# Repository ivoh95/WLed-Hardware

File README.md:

# WLed-Hardware
Collection of PCB designs and other hardware for the WLED project by Aircoookie

WLED Mini is a board intended for use with the wemos D1

WLED 01 is a board intended for use with the esp01

Currently WIP

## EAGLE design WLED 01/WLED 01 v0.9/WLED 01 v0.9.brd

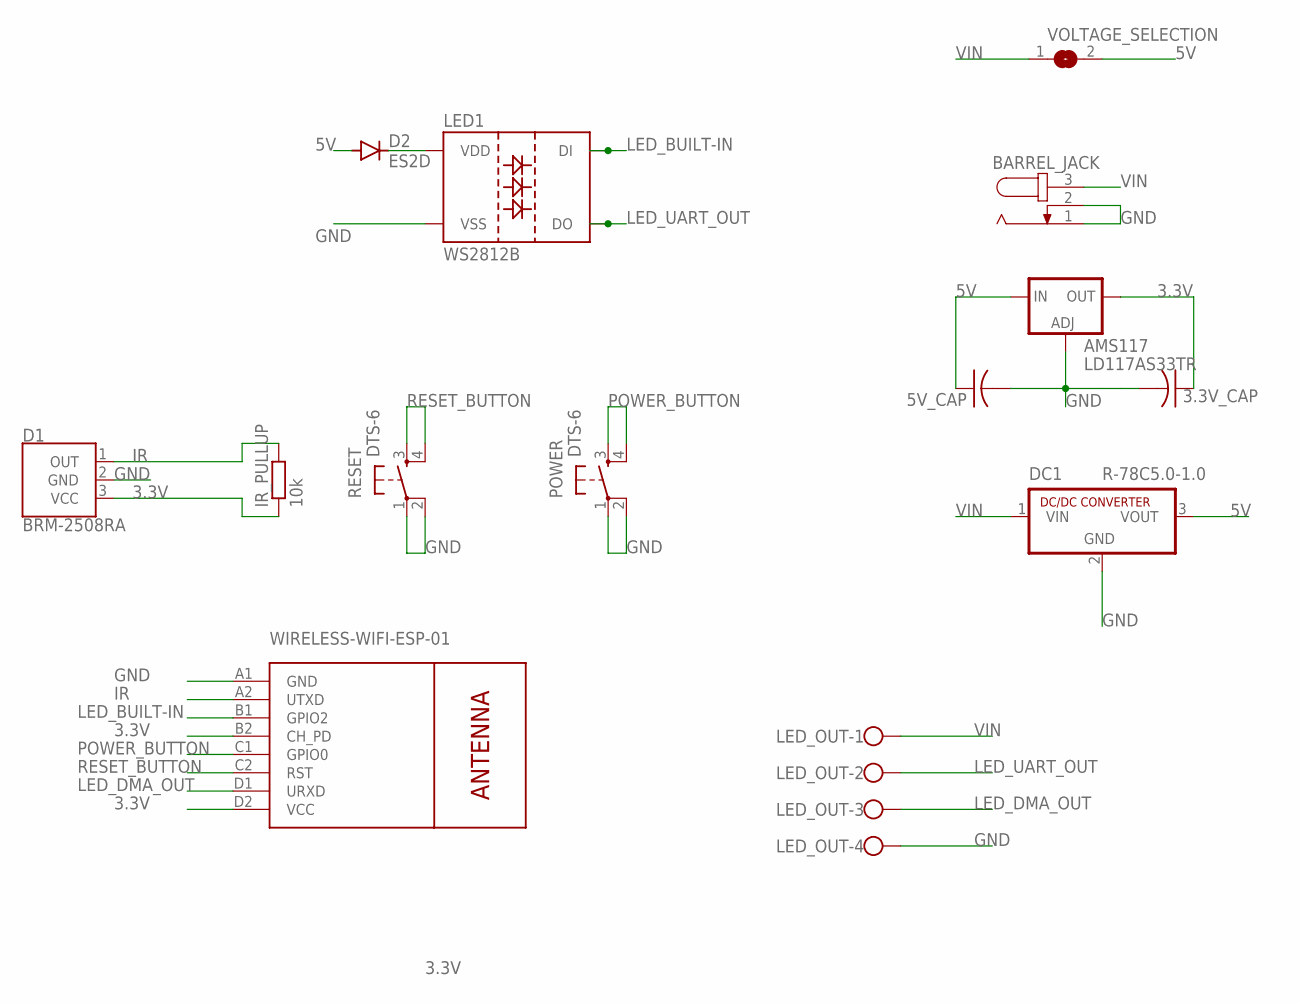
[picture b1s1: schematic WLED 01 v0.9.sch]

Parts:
3.3V_CAP, 5V_CAP: C-USC0805K; C0805K
AMS117: LD117AS33TR; SOT223
BARREL_JACK: JACK-PLUG0; SPC4077
D1: BRM-2508RA; BRM-2508
D2: ES2D; SMB
DC1: R-78C5.0-1.0; SIP3
IR_PULLUP: 10k; R0603
LED1: WS2812B
LED_OUT: W237-4
POWER: DTS-6
RESET: DTS-6
U$1: WIRELESS-WIFI-ESP-01
VOLTAGE_SELECTION: SJ

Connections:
3.3V: 3.3V_CAP.1, AMS117.4 (OUT), D1.3 (VCC), IR_PULLUP.1, U$1.B2 (CH_PD), U$1.D2 (VCC)
5V: 5V_CAP.1, AMS117.3 (IN), D2.A, DC1.3 (VOUT), VOLTAGE_SELECTION.2
GND: 3.3V_CAP.2, 5V_CAP.2, AMS117.1 (ADJ), BARREL_JACK.1, BARREL_JACK.2, D1.2 (GND), DC1.2 (GND), LED1.3 (VSS), LED_OUT.4, POWER.1, POWER.2, RESET.1, RESET.2, U$1.A1 (GND)
IR: D1.1 (OUT), IR_PULLUP.2, U$1.A2 (UTXD)
LED_BUILT-IN: LED1.4 (DI), U$1.B1 (GPIO2)
LED_DMA_OUT: LED_OUT.3, U$1.D1 (URXD)
LED_UART_OUT: LED1.2 (DO), LED_OUT.2
unnamed: D2.C, LED1.1 (VDD)
POWER_BUTTON: POWER.3, POWER.4, U$1.C1 (GPIO0)
RESET_BUTTON: RESET.3, RESET.4, U$1.C2 (RST)
VIN: BARREL_JACK.3, DC1.1 (VIN), LED_OUT.1, VOLTAGE_SELECTION.1

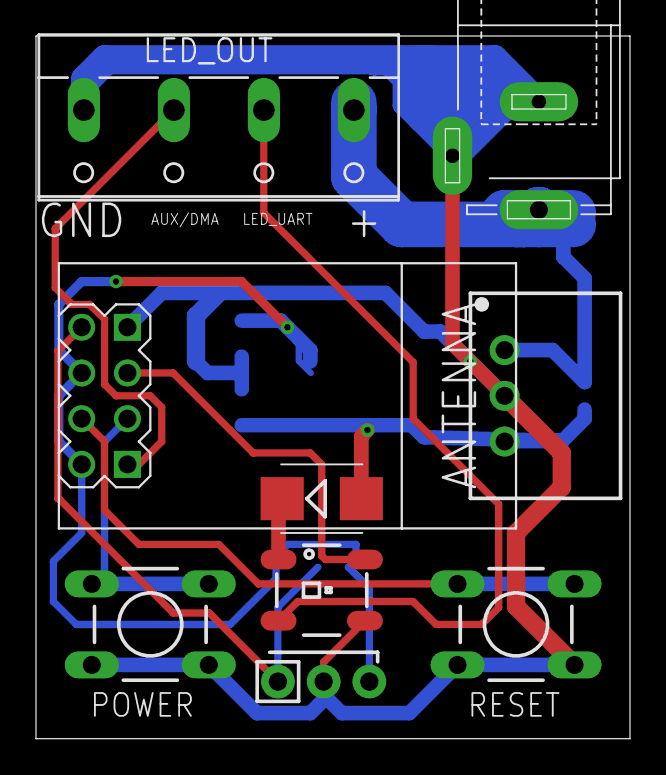
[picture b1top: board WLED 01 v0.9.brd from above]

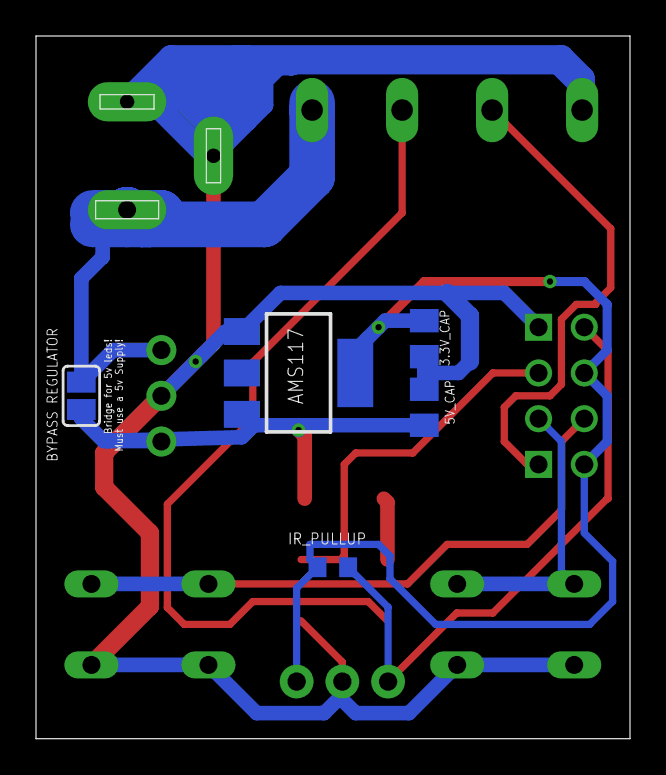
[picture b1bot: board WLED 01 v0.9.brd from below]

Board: 2 copper layers, 33.0 x 39.0 mm, 14 parts (5 on the bottom side), 11 nets.

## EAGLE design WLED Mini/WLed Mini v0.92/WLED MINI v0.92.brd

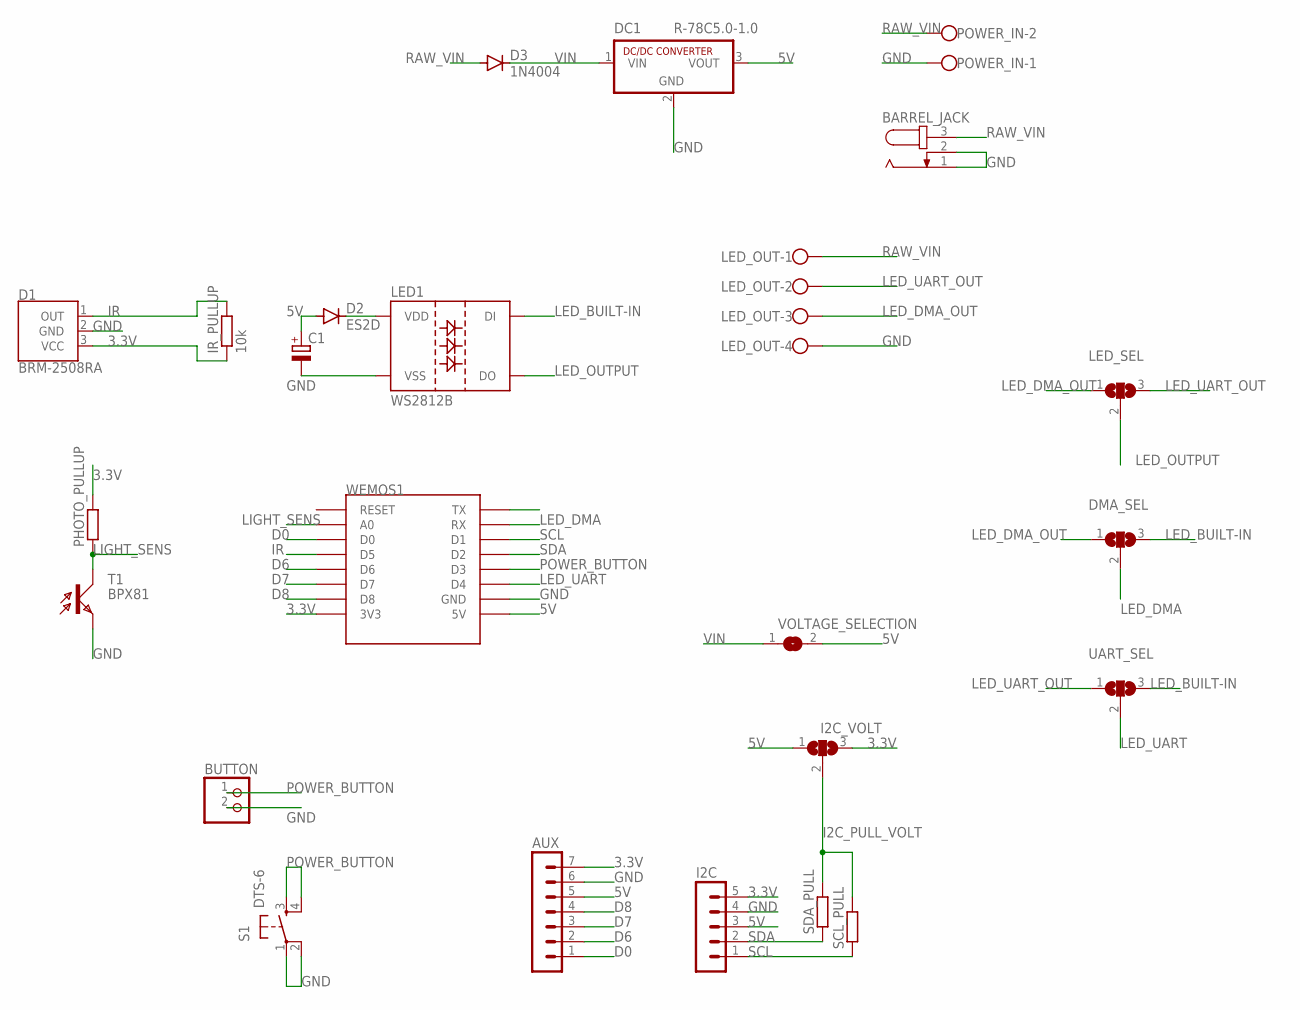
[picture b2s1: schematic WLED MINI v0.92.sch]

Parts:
AUX: MA07-1
BARREL_JACK: JACK-PLUG0; SPC4077
BUTTON: PINHD-1X2; 1X02
C1: CPOL-EUE2.5-7; E2,5-7
D1: BRM-2508RA; BRM-2508
D2: ES2D; SMB
D3: 1N4004; DO41-10
DC1: R-78C5.0-1.0; SIP3
DMA_SEL: SJ2W; SJ_2
I2C: MA05-1
I2C_VOLT: SJ2W; SJ_2
IR_PULLUP: 10k; 0204/7
LED1: WS2812B
LED_OUT: W237-4
LED_SEL: SJ2W; SJ_2
PHOTO_PULLUP: R0204/7; 0204/7
POWER_IN: W237-102
S1: DTS-6
SCL_PULL: R0204/7; 0204/7
SDA_PULL: R0204/7; 0204/7
T1: BPX81
UART_SEL: SJ2W; SJ_2
VOLTAGE_SELECTION: SJ
WEMOS1: WEMOS-D1-MINI

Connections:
3.3V: AUX.7, D1.3 (VCC), I2C.5, I2C_VOLT.3, IR_PULLUP.1, PHOTO_PULLUP.2, WEMOS1.3V3
5V: AUX.5, C1.+, D2.A, DC1.3 (VOUT), I2C.3, I2C_VOLT.1, VOLTAGE_SELECTION.2, WEMOS1.5V
D0: AUX.1, WEMOS1.D0
D6: AUX.2, WEMOS1.D6
D7: AUX.3, WEMOS1.D7
D8: AUX.4, WEMOS1.D8
GND: AUX.6, BARREL_JACK.1, BARREL_JACK.2, BUTTON.2, C1.-, D1.2 (GND), DC1.2 (GND), I2C.4, LED1.3 (VSS), LED_OUT.4, POWER_IN.1, S1.1, S1.2, T1.E, WEMOS1.GND
I2C_PULL_VOLT: I2C_VOLT.2, SCL_PULL.2, SDA_PULL.2
IR: D1.1 (OUT), IR_PULLUP.2, WEMOS1.D5
LED_BUILT-IN: DMA_SEL.3, LED1.4 (DI), UART_SEL.3
LED_DMA: DMA_SEL.2, WEMOS1.RX
LED_DMA_OUT: DMA_SEL.1, LED_OUT.3, LED_SEL.1
LED_OUTPUT: LED1.2 (DO), LED_SEL.2
LED_UART: UART_SEL.2, WEMOS1.D4
LED_UART_OUT: LED_OUT.2, LED_SEL.3, UART_SEL.1
LIGHT_SENS: PHOTO_PULLUP.1, T1.C, WEMOS1.A0
unnamed: D2.C, LED1.1 (VDD)
POWER_BUTTON: BUTTON.1, S1.3, S1.4, WEMOS1.D3
RAW_VIN: BARREL_JACK.3, D3.A, LED_OUT.1, POWER_IN.2
SCL: I2C.1, SCL_PULL.1, WEMOS1.D1
SDA: I2C.2, SDA_PULL.1, WEMOS1.D2
VIN: D3.C, DC1.1 (VIN), VOLTAGE_SELECTION.1

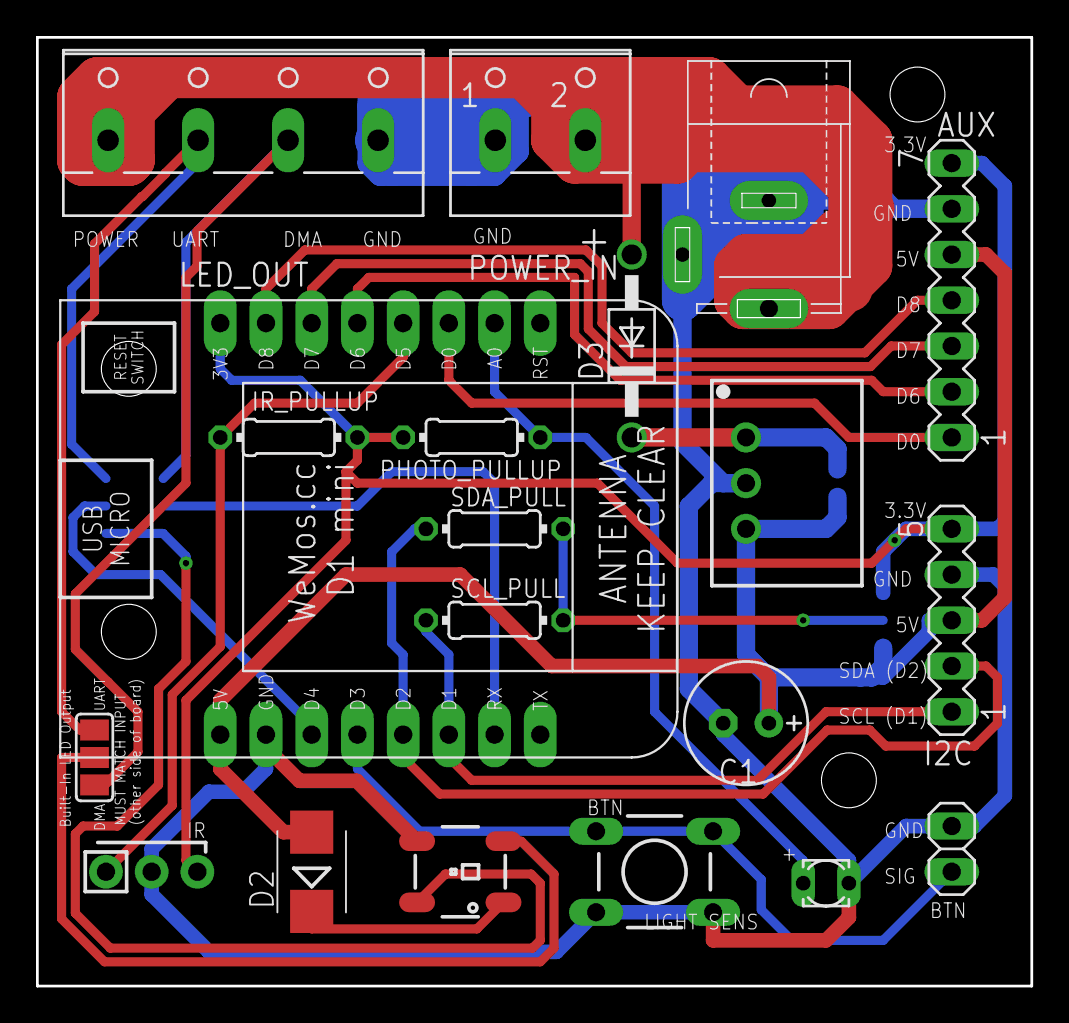
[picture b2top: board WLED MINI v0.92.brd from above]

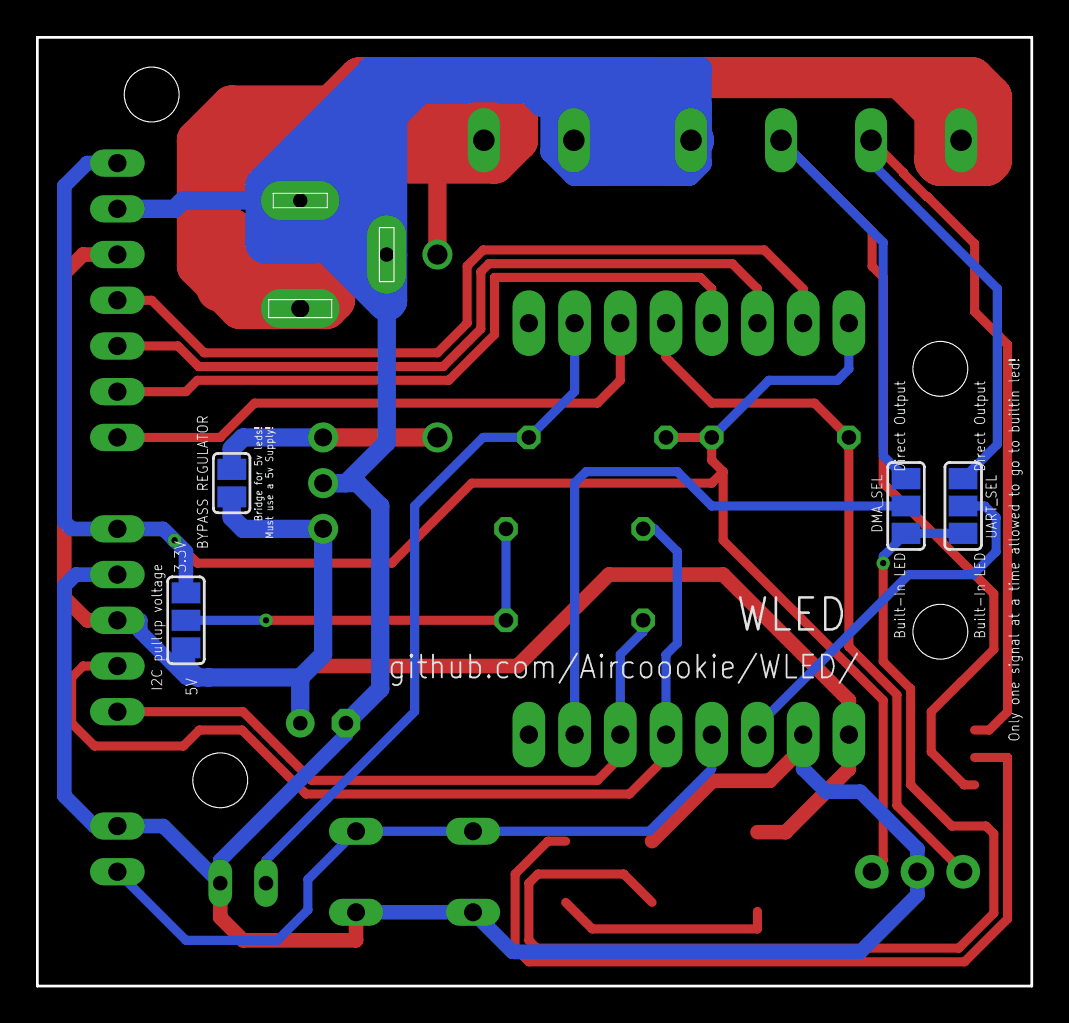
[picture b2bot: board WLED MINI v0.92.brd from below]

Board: 2 copper layers, 55.2 x 52.7 mm, 24 parts (4 on the bottom side), 22 nets.

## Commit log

2019-04-26 Initial upload of pcb files
    Need to be tested and documented.
2019-05-03 Create PCB Build Info
    Added some basic info on the jumpers.

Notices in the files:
parts and their libraries:
diy-modules_mod: Released under the Creative Commons Attribution 4.0 International License: http://creativecommons.org/licenses/by/4.0
SparkFun-Sensors: Licensing: Creative Commons ShareAlike 4.0 International - https://creativecommons.org/licenses/by-sa/4.0
